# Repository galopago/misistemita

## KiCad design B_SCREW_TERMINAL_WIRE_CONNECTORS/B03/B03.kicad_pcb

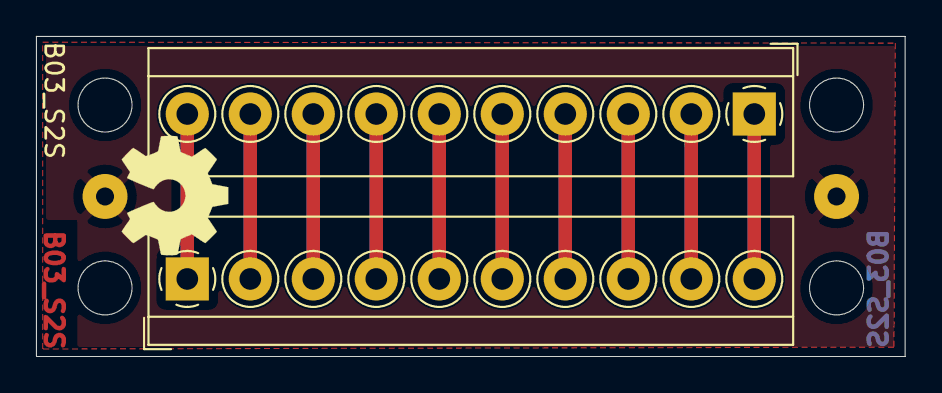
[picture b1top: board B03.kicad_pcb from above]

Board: 2 copper layers, 48.3 x 17.8 mm, 8 parts (0 on the bottom side), 11 nets.

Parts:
HA0, HA4: MountingHole; MountingHole_3mm
HB0, HB4: MountingHole; MountingHole_3mm
J0, J1: Conn_01x01_Male; SolderWirePad_1x01_Drill1mm
J2, J3: Conn_01x10_Female; TerminalBlock_4Ucon_1x10_P3.50mm_Horizontal

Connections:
unnamed: J0.1, J1.1
unnamed: J2.1, J3.10
unnamed: J2.2, J3.9
unnamed: J2.3, J3.8
unnamed: J2.4, J3.7
unnamed: J2.5, J3.6
unnamed: J2.6, J3.5
unnamed: J2.7, J3.4
unnamed: J2.8, J3.3
unnamed: J2.9, J3.2
unnamed: J2.10, J3.1

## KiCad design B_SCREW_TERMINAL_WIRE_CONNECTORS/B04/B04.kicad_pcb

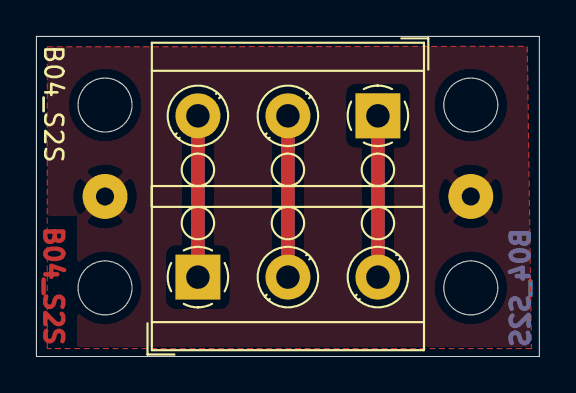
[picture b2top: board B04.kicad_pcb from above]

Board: 2 copper layers, 27.9 x 17.8 mm, 8 parts (0 on the bottom side), 4 nets.

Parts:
HA0, HA2: MountingHole; MountingHole_3mm
HB0, HB2: MountingHole; MountingHole_3mm
J0, J1: Conn_01x01_Male; SolderWirePad_1x01_Drill1mm
J2, J3: Conn_01x03_Female; TerminalBlock_RND_205-00002_1x03_P5.00mm_Horizontal

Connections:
unnamed: J0.1, J1.1
unnamed: J2.1, J3.3
unnamed: J2.2, J3.2
unnamed: J2.3, J3.1

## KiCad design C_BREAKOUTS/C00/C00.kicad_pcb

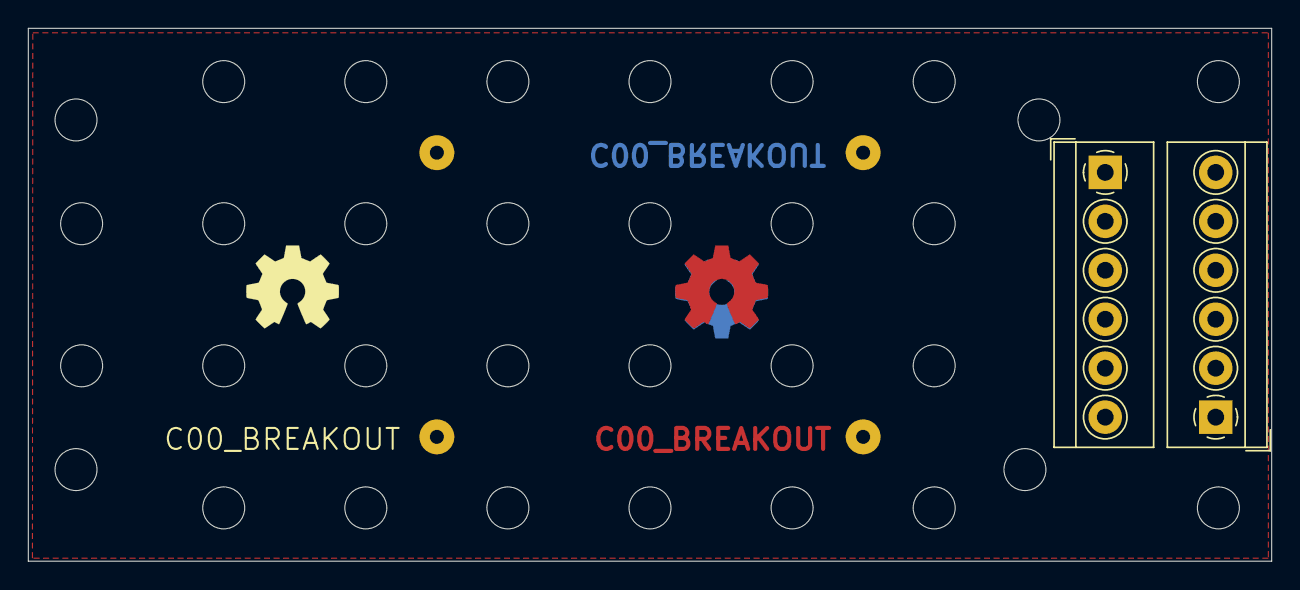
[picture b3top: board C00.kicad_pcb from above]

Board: 2 copper layers, 88.9 x 38.1 mm, 38 parts (0 on the bottom side), 7 nets, no tracks yet.

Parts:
HA1, HA2, HA3, HA4, HA5, HA6, HA8: MountingHole; MountingHole_3mm
HB0, HB1, HB2, HB3, HB4, HB5, HB6: MountingHole; MountingHole_3mm
HC0, HC1, HC2, HC3, HC4, HC5, HC6: MountingHole; MountingHole_3mm
HD1, HD2, HD3, HD4, HD5, HD6, HD8: MountingHole; MountingHole_3mm
HZ0, HZ1, HZ2, HZ3: MountingHole; MountingHole_3mm
J0, J1, J2, J3: Conn_01x01_Male; SolderWirePad_1x01_Drill1mm
J6, J7: Conn_01x06_Female; TerminalBlock_4Ucon_1x06_P3.50mm_Horizontal

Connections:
unnamed: J0.1, J1.1, J2.1, J3.1
unnamed: J6.1, J7.6
unnamed: J6.2, J7.5
unnamed: J6.3, J7.4
unnamed: J6.4, J7.3
unnamed: J6.5, J7.2
unnamed: J6.6, J7.1

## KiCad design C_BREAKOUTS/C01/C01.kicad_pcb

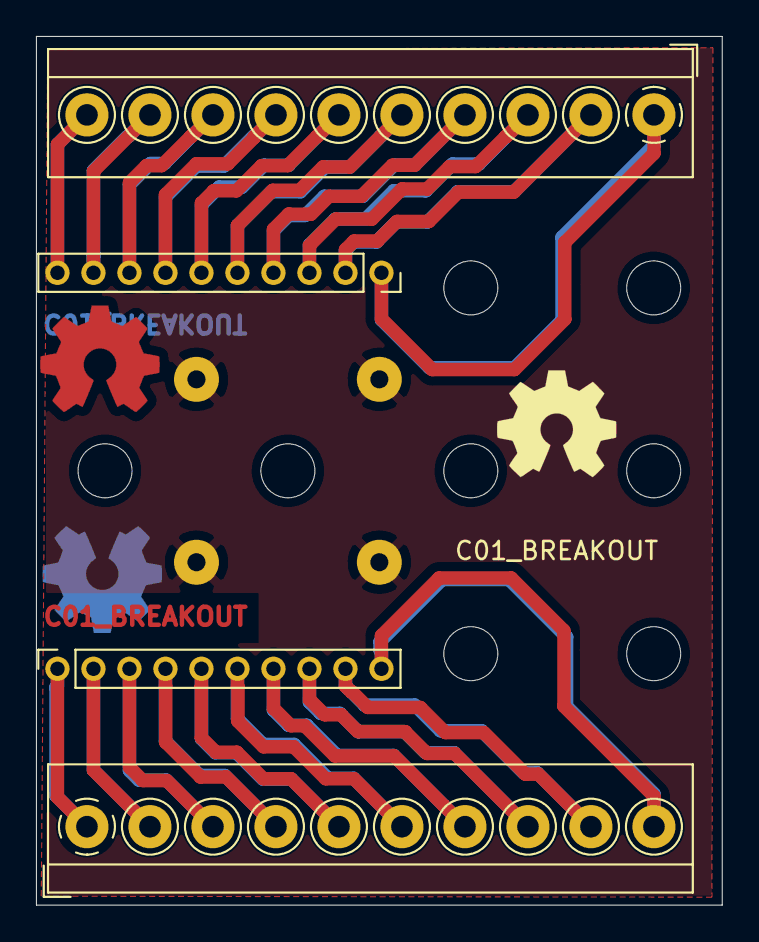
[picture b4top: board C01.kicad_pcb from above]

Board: 2 copper layers, 38.1 x 48.3 mm, 16 parts (0 on the bottom side), 21 nets.

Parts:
HB2, HB3: MountingHole; MountingHole_3mm
HC0, HC1, HC2, HC3: MountingHole; MountingHole_3mm
HD2, HD3: MountingHole; MountingHole_3mm
J0, J1, J2, J3: Conn_01x01_Male; SolderWirePad_1x01_Drill1mm
J4, J5: Conn_01x10_Female; TerminalBlock_4Ucon_1x10_P3.50mm_Horizontal
J6, J7: Conn_01x10_Female; PinSocket_1x10_P2.00mm_Vertical

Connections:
unnamed: J0.1, J1.1, J2.1, J3.1
unnamed: J4.1, J6.1
unnamed: J4.2, J6.2
unnamed: J4.3, J6.3
unnamed: J4.4, J6.4
unnamed: J4.5, J6.5
unnamed: J4.6, J6.6
unnamed: J4.7, J6.7
unnamed: J4.8, J6.8
unnamed: J4.9, J6.9
unnamed: J4.10, J6.10
unnamed: J5.1, J7.1
unnamed: J5.2, J7.2
unnamed: J5.3, J7.3
unnamed: J5.4, J7.4
unnamed: J5.5, J7.5
unnamed: J5.6, J7.6
unnamed: J5.7, J7.7
unnamed: J5.8, J7.8
unnamed: J5.9, J7.9
unnamed: J5.10, J7.10

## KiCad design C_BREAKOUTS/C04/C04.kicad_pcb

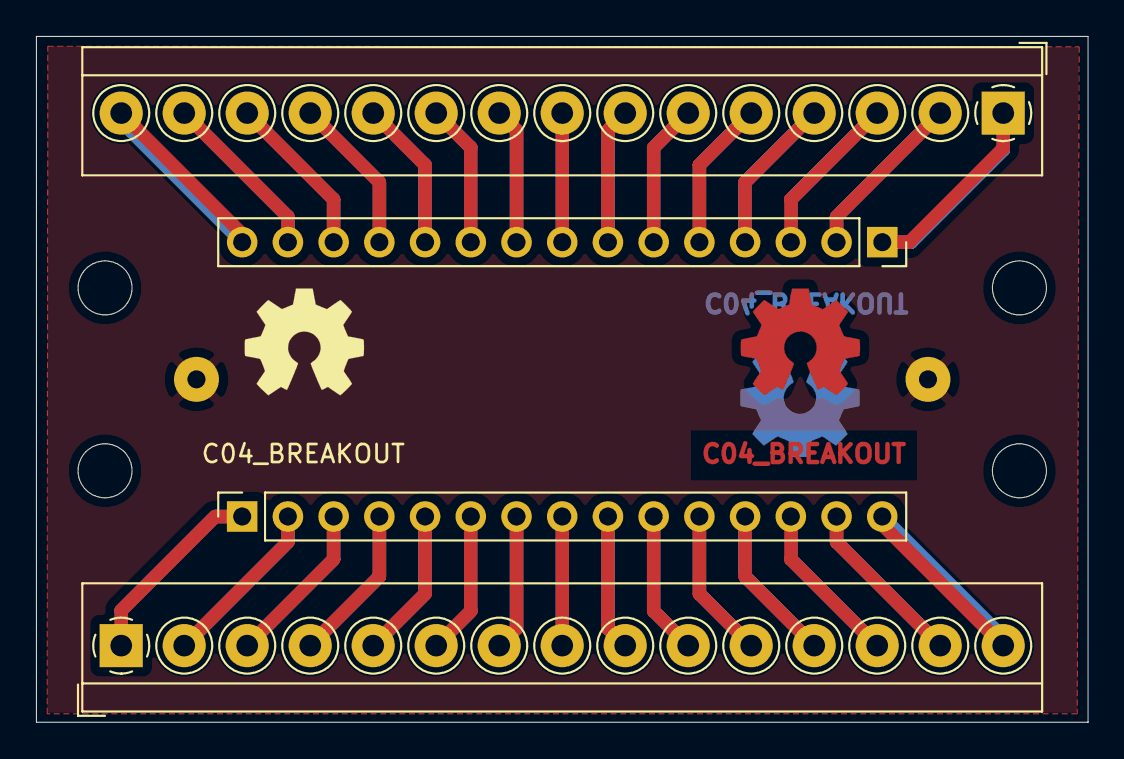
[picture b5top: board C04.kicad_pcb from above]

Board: 2 copper layers, 58.4 x 38.1 mm, 10 parts (0 on the bottom side), 31 nets.

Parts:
HB0, HB5: MountingHole; MountingHole_3mm
HC0, HC5: MountingHole; MountingHole_3mm
J0, J1: Conn_01x01_Male; SolderWirePad_1x01_Drill1mm
J4, J7: Conn_01x15_Female; TerminalBlock_4Ucon_1x15_P3.50mm_Horizontal
J5, J6: Conn_01x15_Female; PinSocket_1x15_P2.54mm_Vertical

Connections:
unnamed: J0.1, J1.1
unnamed: J4.1, J5.1
unnamed: J4.2, J5.2
unnamed: J4.3, J5.3
unnamed: J4.4, J5.4
unnamed: J4.5, J5.5
unnamed: J4.6, J5.6
unnamed: J4.7, J5.7
unnamed: J4.8, J5.8
unnamed: J4.9, J5.9
unnamed: J4.10, J5.10
unnamed: J4.11, J5.11
unnamed: J4.12, J5.12
unnamed: J4.13, J5.13
unnamed: J4.14, J5.14
unnamed: J4.15, J5.15
unnamed: J6.1, J7.1
unnamed: J6.2, J7.2
unnamed: J6.3, J7.3
unnamed: J6.4, J7.4
unnamed: J6.5, J7.5
unnamed: J6.6, J7.6
unnamed: J6.7, J7.7
unnamed: J6.8, J7.8
unnamed: J6.9, J7.9
unnamed: J6.10, J7.10
unnamed: J6.11, J7.11
unnamed: J6.12, J7.12
unnamed: J6.13, J7.13
unnamed: J6.14, J7.14
unnamed: J6.15, J7.15

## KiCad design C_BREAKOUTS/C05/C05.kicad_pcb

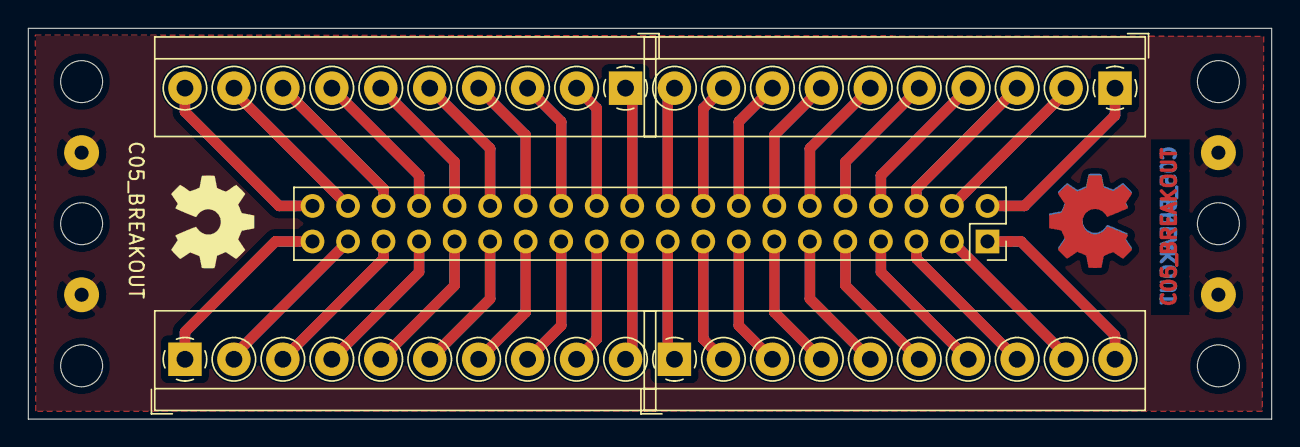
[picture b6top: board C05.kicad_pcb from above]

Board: 2 copper layers, 88.9 x 27.9 mm, 15 parts (0 on the bottom side), 41 nets.

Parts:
HA0, HA8: MountingHole; MountingHole_3mm
HB0, HB8: MountingHole; MountingHole_3mm
HC0, HC8: MountingHole; MountingHole_3mm
J0, J1, J2, J3: Conn_01x01_Male; SolderWirePad_1x01_Drill1mm
J4, J6, J7, J8: Conn_01x10_Female; TerminalBlock_4Ucon_1x10_P3.50mm_Horizontal
J5: Conn_02x20_Odd_Even; PinSocket_2x20_P2.54mm_Vertical

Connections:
unnamed: J0.1, J1.1, J2.1, J3.1
unnamed: J4.1, J5.19
unnamed: J4.2, J5.17
unnamed: J4.3, J5.15
unnamed: J4.4, J5.13
unnamed: J4.5, J5.11
unnamed: J4.6, J5.9
unnamed: J4.7, J5.7
unnamed: J4.8, J5.5
unnamed: J4.9, J5.3
unnamed: J4.10, J5.1
unnamed: J5.2, J7.1
unnamed: J5.4, J7.2
unnamed: J5.6, J7.3
unnamed: J5.8, J7.4
unnamed: J5.10, J7.5
unnamed: J5.12, J7.6
unnamed: J5.14, J7.7
unnamed: J5.16, J7.8
unnamed: J5.18, J7.9
unnamed: J5.20, J7.10
unnamed: J5.21, J6.10
unnamed: J5.22, J8.1
unnamed: J5.23, J6.9
unnamed: J5.24, J8.2
unnamed: J5.25, J6.8
unnamed: J5.26, J8.3
unnamed: J5.27, J6.7
unnamed: J5.28, J8.4
unnamed: J5.29, J6.6
unnamed: J5.30, J8.5
unnamed: J5.31, J6.5
unnamed: J5.32, J8.6
unnamed: J5.33, J6.4
unnamed: J5.34, J8.7
unnamed: J5.35, J6.3
unnamed: J5.36, J8.8
unnamed: J5.37, J6.2
unnamed: J5.38, J8.9
unnamed: J5.39, J6.1
unnamed: J5.40, J8.10

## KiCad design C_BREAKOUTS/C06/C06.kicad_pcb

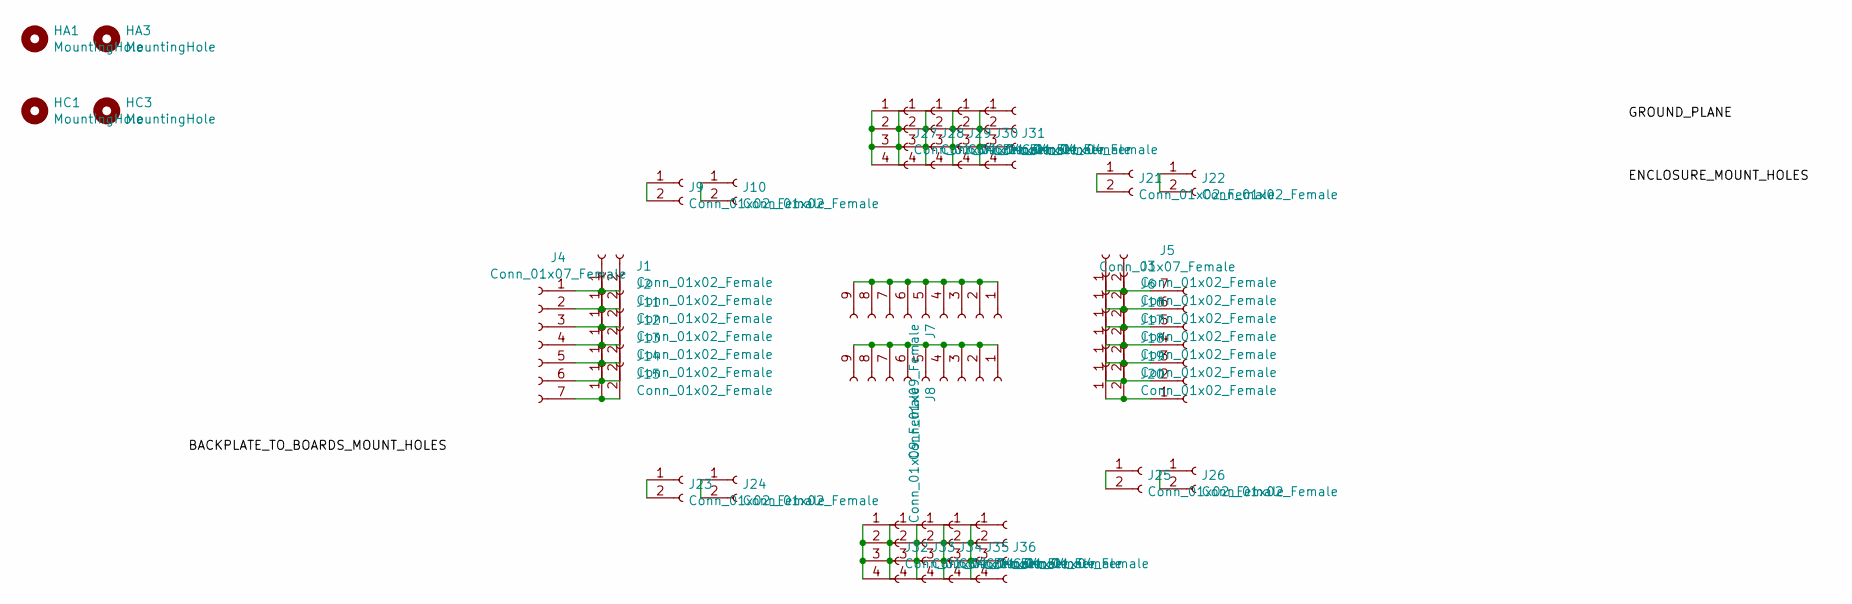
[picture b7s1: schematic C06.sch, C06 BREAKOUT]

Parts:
HA1, HA3: MountingHole; MountingHole_3mm
HC1, HC3: MountingHole; MountingHole_3mm
J1, J2, J3, J6, J9, J10, J11, J12, J13, J14, J15, J16, J17, J18, J19, J20, J21, J22, J23, J24, J25, J26: Conn_01x02_Female; PinHeader_1x02_P2.54mm_Vertical
J4, J5: Conn_01x07_Female; TerminalBlock_4Ucon_1x07_P3.50mm_Horizontal
J7, J8: Conn_01x09_Female; PinHeader_1x09_P2.54mm_Vertical
J27, J28, J29, J30, J31, J32, J33, J34, J35, J36: Conn_01x04_Female; PinHeader_1x04_P2.54mm_Vertical

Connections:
unnamed: J1.1, J1.2, J4.1
unnamed: J2.1, J2.2, J4.2
unnamed: J3.1, J3.2, J5.7
unnamed: J5.6, J6.1, J6.2
unnamed: J7.1, J7.2, J7.3, J7.4, J7.5, J7.6, J7.7, J7.8, J7.9
unnamed: J8.1, J8.2, J8.3, J8.4, J8.5, J8.6, J8.7, J8.8, J8.9
unnamed: J9.1, J9.2
unnamed: J10.1, J10.2
unnamed: J4.3, J11.1, J11.2
unnamed: J4.4, J12.1, J12.2
unnamed: J4.5, J13.1, J13.2
unnamed: J4.6, J14.1, J14.2
unnamed: J4.7, J15.1, J15.2
unnamed: J5.5, J16.1, J16.2
unnamed: J5.4, J17.1, J17.2
unnamed: J5.3, J18.1, J18.2
unnamed: J5.2, J19.1, J19.2
unnamed: J5.1, J20.1, J20.2
unnamed: J21.1, J21.2
unnamed: J22.1, J22.2
unnamed: J23.1, J23.2
unnamed: J24.1, J24.2
unnamed: J25.1, J25.2
unnamed: J26.1, J26.2
unnamed: J27.1, J27.2, J27.3, J27.4
unnamed: J28.1, J28.2, J28.3, J28.4
unnamed: J29.1, J29.2, J29.3, J29.4
unnamed: J30.1, J30.2, J30.3, J30.4
unnamed: J31.1, J31.2, J31.3, J31.4
unnamed: J32.1, J32.2, J32.3, J32.4
unnamed: J33.1, J33.2, J33.3, J33.4
unnamed: J34.1, J34.2, J34.3, J34.4
unnamed: J35.1, J35.2, J35.3, J35.4
unnamed: J36.1, J36.2, J36.3, J36.4

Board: 2 copper layers, 40 parts (0 on the bottom side), 34 nets, no tracks yet.
